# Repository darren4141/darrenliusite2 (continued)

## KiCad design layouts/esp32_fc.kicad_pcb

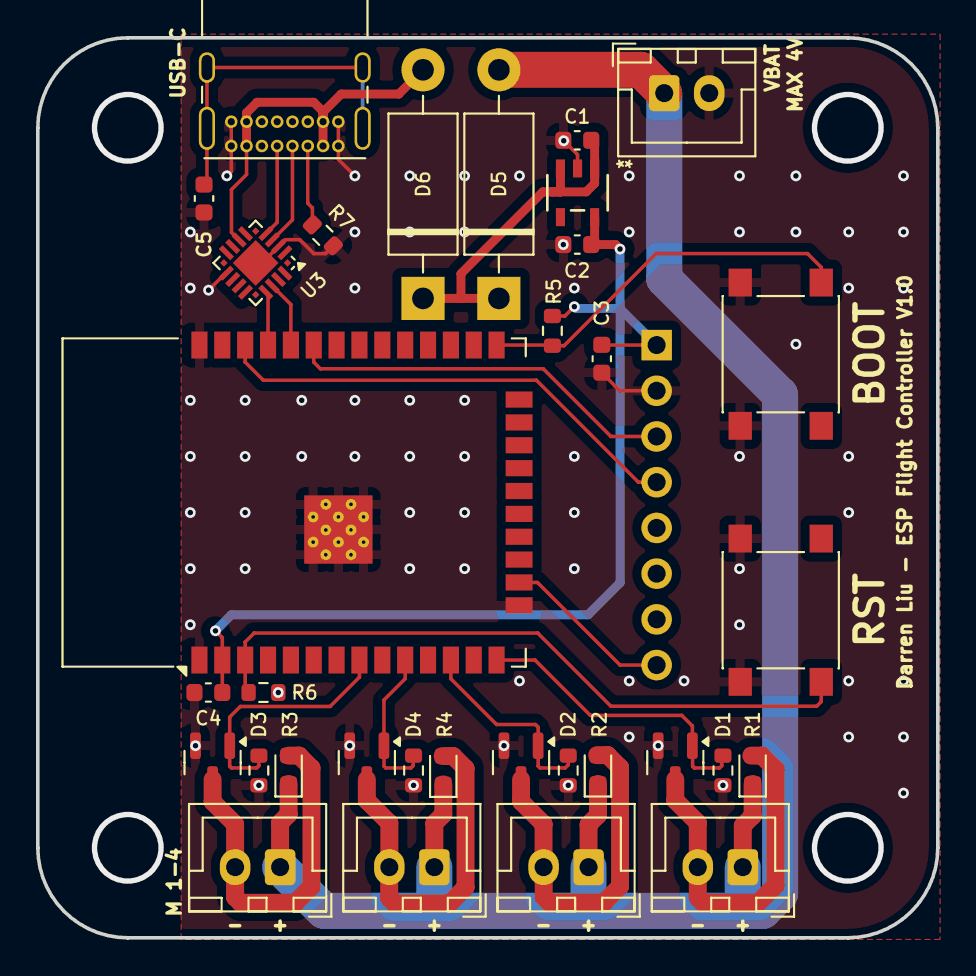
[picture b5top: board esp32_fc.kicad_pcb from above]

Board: 2 copper layers, 50.0 x 50.0 mm, 34 parts (1 on the bottom side), 24 nets.

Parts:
C1, C2, C3, C4, C5: 1uF; C_0603_1608Metric
D1, D2, D3, D4: LED; LED_0603_1608Metric
D5, D6: D; D_DO-15_P12.70mm_Horizontal
J1, J2, J3, J4, J5: Conn_01x02_Pin; JST_XH_B2B-XH-A_1x02_P2.50mm_Vertical
J6: Conn_01x08_Socket; PinSocket_1x08_P2.54mm_Vertical
J7: USB_C_Receptacle_USB2.0_16P; USB_C_Receptacle_GCT_USB4085
Q1, Q2, Q3, Q4: IRLML6244; SOT-23
R1, R2, R3, R4: 10K; R_0603_1608Metric
R5, R6: R; R_0603_1608Metric
R7: 5.1K; R_0603_1608Metric
SW1, SW2: SW_SPST; SW_SPST_PTS645
U1: ESP32-WROOM-32D
U2: AP2112K-3.3TRG1; SOT_RG1_DIO
U3: CP2102N-Axx-xQFN20; SiliconLabs_QFN-20-1EP_3x3mm_P0.5mm_EP1.8x1.8mm

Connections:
3.7V: D1.1 (K), D2.1 (K), D3.1 (K), D4.1 (K), D5.2 (A), J1.1, J2.1, J3.1, J4.1, J5.1
3V3: C2.2, C3.2, C4.1, J6.1, R5.2, R6.2, U1.2 (VDD), U2.5 (VOUT)
5V: D6.2 (A), J7.A4 (VBUS), J7.A9 (VBUS), J7.B4 (VBUS), J7.B9 (VBUS), U3.8 (VBUS)
D+: J7.A6 (D+), U3.4 (D+)
D-: J7.A7 (D-), U3.5 (D-)
GND: C1.1, C2.1, C3.1, C4.2, C5.2, J5.2, J6.2, J7.A1 (GND), J7.A12 (GND), J7.B1 (GND), J7.B12 (GND), Q1.2 (S), Q2.2 (S), Q3.2 (S), Q4.2 (S), R1.2, R2.2, R3.2, R4.2, R7.2, SW1.1 (A), SW2.2 (B), U1.1 (GND), U1.15 (GND), U1.38 (GND), U1.39 (GND), U2.2 (GND), U3.3 (GND), U3.12 (GND), U3.21 (GND)
GPIO1: U1.35 (TXD0/IO1), U3.17 (RXD)
GPIO3: U1.34 (RXD0/IO3), U3.18 (TXD)
GPIO12: Q1.1 (G), R1.1, U1.14 (IO12)
GPIO21: J6.3, U1.33 (IO21)
GPIO22: J6.4, U1.36 (IO22)
GPIO25: Q4.1 (G), R4.1, U1.10 (IO25)
GPIO27: Q2.1 (G), R2.1, U1.12 (IO27)
GPIO32: Q3.1 (G), R3.1, U1.8 (IO32)
INT: J6.8, U1.16 (IO13)
unnamed: D1.2 (A), J1.2, Q1.3 (D)
unnamed: D2.2 (A), J2.2, Q2.3 (D)
unnamed: D3.2 (A), J3.2, Q3.3 (D)
unnamed: D4.2 (A), J4.2, Q4.3 (D)
unnamed: C1.2, D5.1 (K), D6.1 (K), U2.1 (VIN), U2.3 (EN)
unnamed: J7.A5 (CC1), R7.1
unnamed: C5.1, J7.S1 (SHIELD)
unnamed: R6.1, SW1.2 (B), U1.3 (EN)
unnamed: R5.1, SW2.1 (A), U1.25 (IO0)

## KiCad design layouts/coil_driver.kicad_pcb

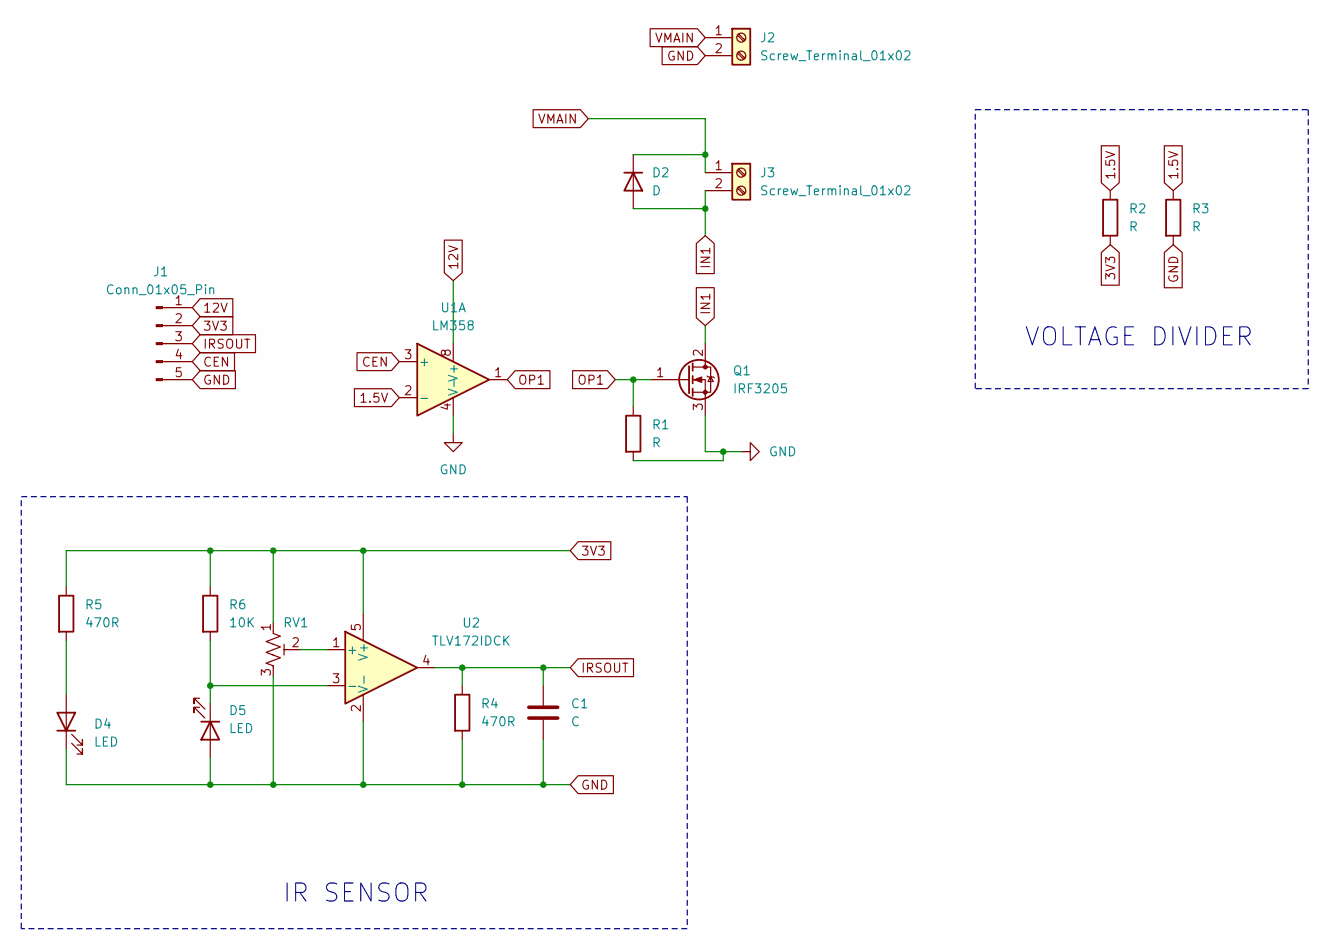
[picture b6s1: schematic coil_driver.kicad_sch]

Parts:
C1: C; C_0603_1608Metric
D2: D; D_0603_1608Metric
D4, D5: LED; LED_D3.0mm
J1: Conn_01x05_Pin; JST_XH_B5B-XH-AM_1x05_P2.50mm_Vertical
J2, J3: Screw_Terminal_01x02; TerminalBlock_Xinya_XY308-2.54-2P_1x02_P2.54mm_Horizontal
Q1: IRF3205; TO-220-3_Vertical
R1, R2, R3: R; R_0603_1608Metric
R4, R5: 470R; R_0603_1608Metric
R6: 10K; R_0603_1608Metric
RV1: R_Potentiometer_Trim_US; Potentiometer_Bourns_3214J_Horizontal
U1: LM358; DIP-8_W7.62mm
U2: TLV172IDCK; SOT-353_SC-70-5

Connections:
1.5V: R2.1, R3.1, U1.2 (-)
3V3: J1.2, R2.2, R5.1, R6.1, RV1.1, U2.5 (V+)
12V: J1.1, U1.8 (V+)
CEN: J1.4, U1.3 (+)
GND: C1.2, D4.1 (K), D5.2 (A), J1.5, J2.2, Q1.3 (S), R1.2, R3.2, R4.2, RV1.3, U1.4 (V-), U2.2 (V-)
IN1: D2.2 (A), J3.2, Q1.2 (D)
IRSOUT: C1.1, J1.3, R4.1, U2.4
unnamed: D4.2 (A), R5.2
unnamed: D5.1 (K), R6.2, U2.3 (-)
unnamed: RV1.2, U2.1 (+)
OP1: Q1.1 (G), R1.1, U1.1
VMAIN: D2.1 (K), J2.1, J3.1

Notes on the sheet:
VOLTAGE DIVIDER
IR SENSOR

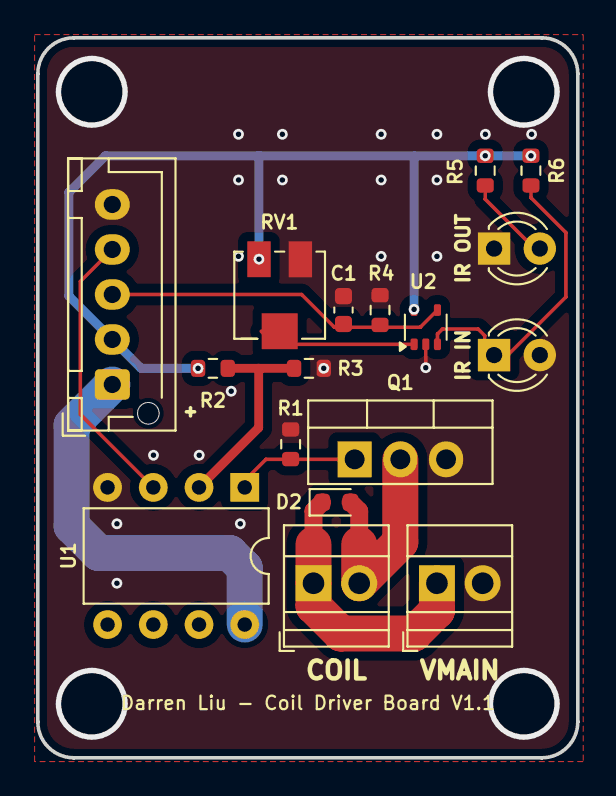
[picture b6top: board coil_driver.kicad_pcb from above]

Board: 2 copper layers, 30.0 x 40.0 mm, 17 parts (0 on the bottom side), 12 nets.

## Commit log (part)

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2024-09-24 aaaa
2024-09-24 added another seciton to project 1
2024-09-24 added 4 & 5
2024-10-01 text formatting
2024-10-01 project 2
2024-10-01 Create CNAME
2024-10-01 added picture for proj 4
2024-10-01 commented some stuff out
2024-10-02 gifs and reactive page
2024-10-02 project images
2024-10-02 added a flowchart
2024-10-05 restyling
2024-10-07 front page reformatting
2024-10-08 more detail in descriptions
2024-10-09 links and icon
2024-10-10 new resume and icon
2024-10-10 more detail and gifs
2024-10-10 subtitles
2024-10-13 test commit
2024-11-09 new res
2024-11-11 enw res
2024-11-17 links
2025-01-19 added images
2025-01-19 low level code section
2025-01-22 image update prj 2
2025-01-22 grammar and shi
2025-01-23 updated images
2025-01-24 more stuff for proj 2
2025-01-26 more description
2025-01-26 more details
2025-01-26 updated link
2025-01-29 webpage stuff
2025-01-29 resize image
2025-01-31 made site reactive
2025-03-04 text fix
2025-04-09 mroe stuff
2025-04-11 new images
2025-05-13 drone section
2025-05-13 project 5
2025-05-13 update to project 6
2025-05-17 animation
2025-05-18 pcb viewer window
2025-05-18 diff board
2025-05-20 coil board
2025-05-20 faster image loading
2025-05-20 new cover photo
2025-05-23 schematics and schematic vuewer test
2025-05-23 kicanvas schematic viewer
2025-05-24 changed one of the schematics
2025-05-24 changed espfc schematic
2025-05-24 schematic and layout viewer
2025-05-24 nojekyll file
2025-05-24 pcb viewer fix
2025-05-27 css redo
2025-07-06 word changing
2025-07-06 words
2025-07-09 secret sauce
2025-07-09 auto spinning + some other stuff
2025-07-09 added pcb viewer
2025-07-09 formatting
2025-07-09 sum text'
2025-07-12 auto rotate
2025-12-26 added cm4 board to pcb viewer
2025-12-30 more viewers
2025-12-30 pcb viewers only rotate when visited
2025-12-30 added modals
2025-12-31 added projects
2025-12-31 added more details and models
2026-01-10 added new project
2026-01-10 project 8 more details
2026-01-10 more detail project 8
2026-01-14 resume upd
2026-05-11 added readme
2026-05-19 moved CNAME
2026-05-19 removed readme
2026-05-19 remove CNAME file
2026-05-20 remove
2026-06-15 start of rework
2026-06-16 reword continued
